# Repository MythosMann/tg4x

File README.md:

The TG4x
A cheap, opensource, qmk powered 40%.
Summary
Basically, this would be a ~$30-35 qmk powered 40% keyboard using parts from a "cop car" keyboard.  The name comes from the fact that it's a step up (TG4x), but also that it's a 40%(think 4x%).  Since the TG3's are so cheap, and they come with switches (mx blacks, too), caps, and plates, they're a great start for a handwired build.  However, not many people have the time or resources to make a handwired build.  I wnated to make something that's more fun than buying a Redragon k552, but at the same price point.  My goal for this project is to drag more people down into the wallet-sucking abyss, without sucking people's wallets.
How it would work:
I'd probably sell it three ways; a barebones kit, a kit with everything you'd need, and fully assembled keyboards.  
- The barebones kits would be the pcbs, diodes, standoffs, and a pre-programmed controller.  You'd need to buy your own TG3 and cut the plates yourself.

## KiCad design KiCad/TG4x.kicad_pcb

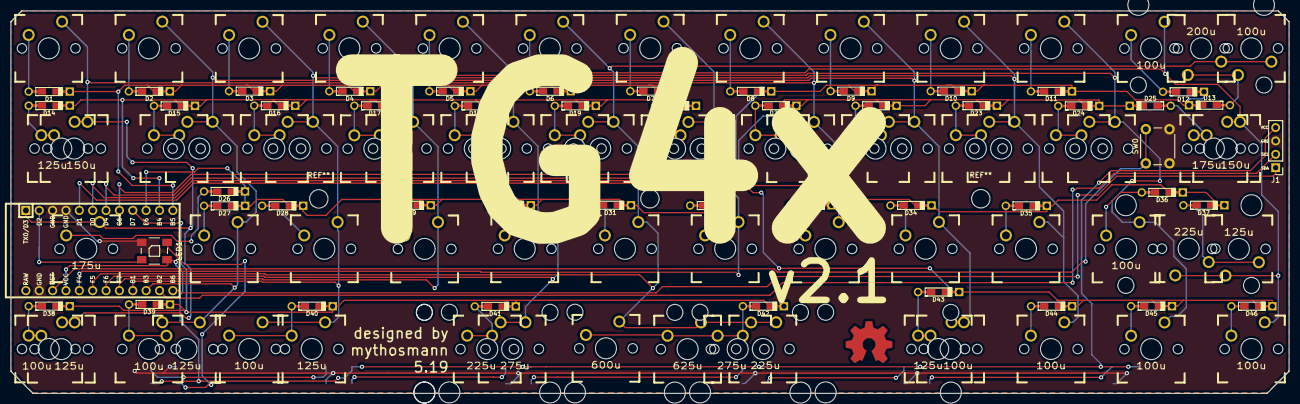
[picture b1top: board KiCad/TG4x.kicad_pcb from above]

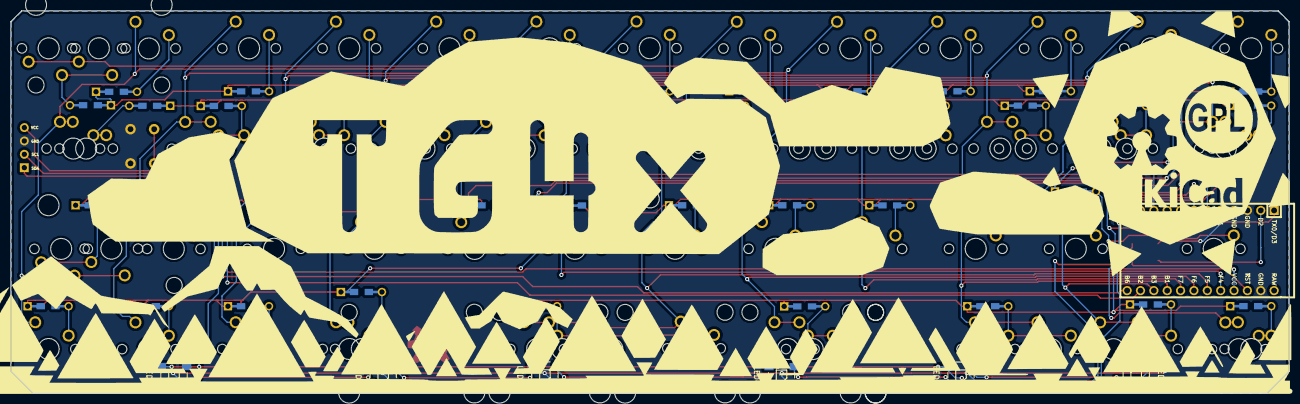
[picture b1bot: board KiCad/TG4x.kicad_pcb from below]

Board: 2 copper layers, 243.0 x 72.7 mm, 124 parts (7 on the bottom side), 73 nets.

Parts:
100u, 100u#2, 100u#3, 100u#4, 100u#5, 100u#6, 100u#7, 100u#8, 100u#9, 100u#10, 125u, 600u: SW_Push; MX_PCB_100H
125u#2, 125u#3, 125u#4, 125u#5, 125u#6: SW_Push; MX_PCB_125H
150u, 175u#2: SW_Push; MX_PCB_150H
150u#2, 175u: SW_Push; MX_PCB_175H
200u: SW_Push; MX_PCB_200H
225u, 225u#2, 225u#3: SW_Push; MX_PCB_225H
275u, 275u#2: SW_Push; MX_PCB_275H
625u: SW_Push; MX_PCB_625H
D1, D2, D3, D4, D5, D6, D7, D8, D9, D10, D11, D12, D13, D14, D15, D16, D17, D18, D19, D20, D21, D22, D23, D24, D25, D26, D27, D28, D29, D30, D31, D32, D33, D34, D35, D36, D37, D38, D39, D40, D41, D42, D43, D44, D45, D46: 1N4148; Diode-dual
J1: Conn_01x04_Female; PinHeader_1x04_P2.54mm_Vertical
LED1, LED2, LED3, LED4, LED5, LED6, LED7: WS2812B
SW0: SW_Push; SW_PUSH_6mm
SW1, SW2, SW3, SW4, SW5, SW6, SW7, SW8, SW9, SW10, SW11, SW15, SW15b1, SW16, SW16b1, SW17, SW17b1, SW18, SW18b1, SW19, SW19b1, SW20, SW20b1, SW21, SW21b1, SW22, SW22b1, SW23, SW23b1, SW24, SW24b1, SW27, SW28, SW29, SW30, SW31, SW32, SW33, SW34, SW35: SW_Push; MX_PCB_100H
U1: ProMicro; ArduinoProMicro

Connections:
COL0: 100u#6.1, 125u#2.1, 125u#4.1, 150u.1, 175u.1, SW1.1, SW8.1, SW21.1, SW21b1.1, SW33.1, U1.1
COL1: 100u#7.1, 100u#9.1, 125u.1, 125u#5.1, SW2.1, SW9.1, SW15.1, SW15b1.1, SW22.1, SW22b1.1, SW27.1, SW34.1, U1.15
COL2: 100u#2.1, 100u#8.1, 125u#6.1, SW3.1, SW10.1, SW16.1, SW16b1.1, SW23.1, SW23b1.1, SW28.1, SW35.1, U1.16
COL3: 100u.1, 100u#3.1, SW4.1, SW11.1, SW17.1, SW17b1.1, SW24.1, SW24b1.1, SW29.1, U1.17
COL4: 100u#4.1, 100u#5.1, 125u#3.1, 150u#2.1, 175u#2.1, 225u.1, 225u#2.1, 275u#2.1, SW5.1, SW18.1, SW18b1.1, SW30.1, U1.18
COL5: 100u#10.2, 200u.2, 225u#3.1, 275u.1, 600u.1, 625u.1, SW6.1, SW19.1, SW19b1.1, SW31.1, U1.19
COL6: SW7.1, SW20.1, SW20b1.1, SW32.1, U1.20
GND: J1.3, LED1.3, LED2.3, LED3.3, LED4.3, LED5.3, LED6.3, LED7.3, SW0.2, U1.3, U1.4, U1.23
LED: LED1.4, U1.2
unnamed: D1.2, SW1.2
unnamed: D2.2, SW2.2
unnamed: D3.2, SW3.2
unnamed: D4.2, SW4.2
unnamed: D5.2, SW5.2
unnamed: D6.2, SW6.2
unnamed: D7.2, SW7.2
unnamed: D8.2, SW8.2
unnamed: D9.2, SW9.2
unnamed: D10.2, SW10.2
unnamed: D11.2, SW11.2
unnamed: 100u#5.2, D12.2
unnamed: 100u#10.1, 200u.1, D13.2
unnamed: 125u#2.2, 150u.2, D14.2
unnamed: D15.2, SW15.2, SW15b1.2
unnamed: D16.2, SW16.2, SW16b1.2
unnamed: D17.2, SW17.2, SW17b1.2
unnamed: D18.2, SW18.2, SW18b1.2
unnamed: D19.2, SW19.2, SW19b1.2
unnamed: D20.2, SW20.2, SW20b1.2
unnamed: D21.2, SW21.2, SW21b1.2
unnamed: D22.2, SW22.2, SW22b1.2
unnamed: D23.2, SW23.2, SW23b1.2
unnamed: D24.2, SW24.2, SW24b1.2
unnamed: 150u#2.2, 175u#2.2, D25.2
unnamed: 175u.2, D26.2
unnamed: D27.2, SW27.2
unnamed: D28.2, SW28.2
unnamed: D29.2, SW29.2
unnamed: D30.2, SW30.2
unnamed: D31.2, SW31.2
unnamed: D32.2, SW32.2
unnamed: D33.2, SW33.2
unnamed: D34.2, SW34.2
unnamed: D35.2, SW35.2
unnamed: 100u.2, D36.2
unnamed: 125u#3.2, 225u.2, D37.2
unnamed: 100u#6.2, 125u#4.2, D38.2
unnamed: 100u#7.2, 125u#5.2, D39.2
unnamed: 100u#8.2, 125u#6.2, D40.2
unnamed: 225u#2.2, 275u#2.2, D41.2
unnamed: 225u#3.2, 275u.2, 600u.2, 625u.2, D42.2
unnamed: 100u#9.2, 125u.2, D43.2
unnamed: 100u#2.2, D44.2
unnamed: 100u#3.2, D45.2
unnamed: 100u#4.2, D46.2
unnamed: LED1.2, LED2.4
unnamed: LED2.2, LED3.4
unnamed: LED3.2, LED4.4
unnamed: LED4.2, LED5.4
unnamed: LED5.2, LED6.4
unnamed: LED6.2, LED7.4
ROW0: D1.1, D2.1, D3.1, D4.1, D5.1, D6.1, D7.1, U1.12
ROW1: D14.1, D15.1, D16.1, D17.1, D18.1, D19.1, D20.1, U1.11
ROW2: D26.1, D27.1, D28.1, D29.1, D30.1, D31.1, D32.1, U1.10
ROW3: D38.1, D39.1, D40.1, D41.1, D42.1, U1.9
ROW4: D8.1, D9.1, D10.1, D11.1, D12.1, D13.1, U1.8
ROW5: D21.1, D22.1, D23.1, D24.1, D25.1, U1.7
ROW6: D33.1, D34.1, D35.1, D36.1, D37.1, U1.6
ROW7: D43.1, D44.1, D45.1, D46.1, U1.5
RST: SW0.1, U1.22
SCL: J1.2, U1.14
SDA: J1.1, U1.13
VCC: J1.4, LED1.1, LED2.1, LED3.1, LED4.1, LED5.1, LED6.1, LED7.1, U1.21

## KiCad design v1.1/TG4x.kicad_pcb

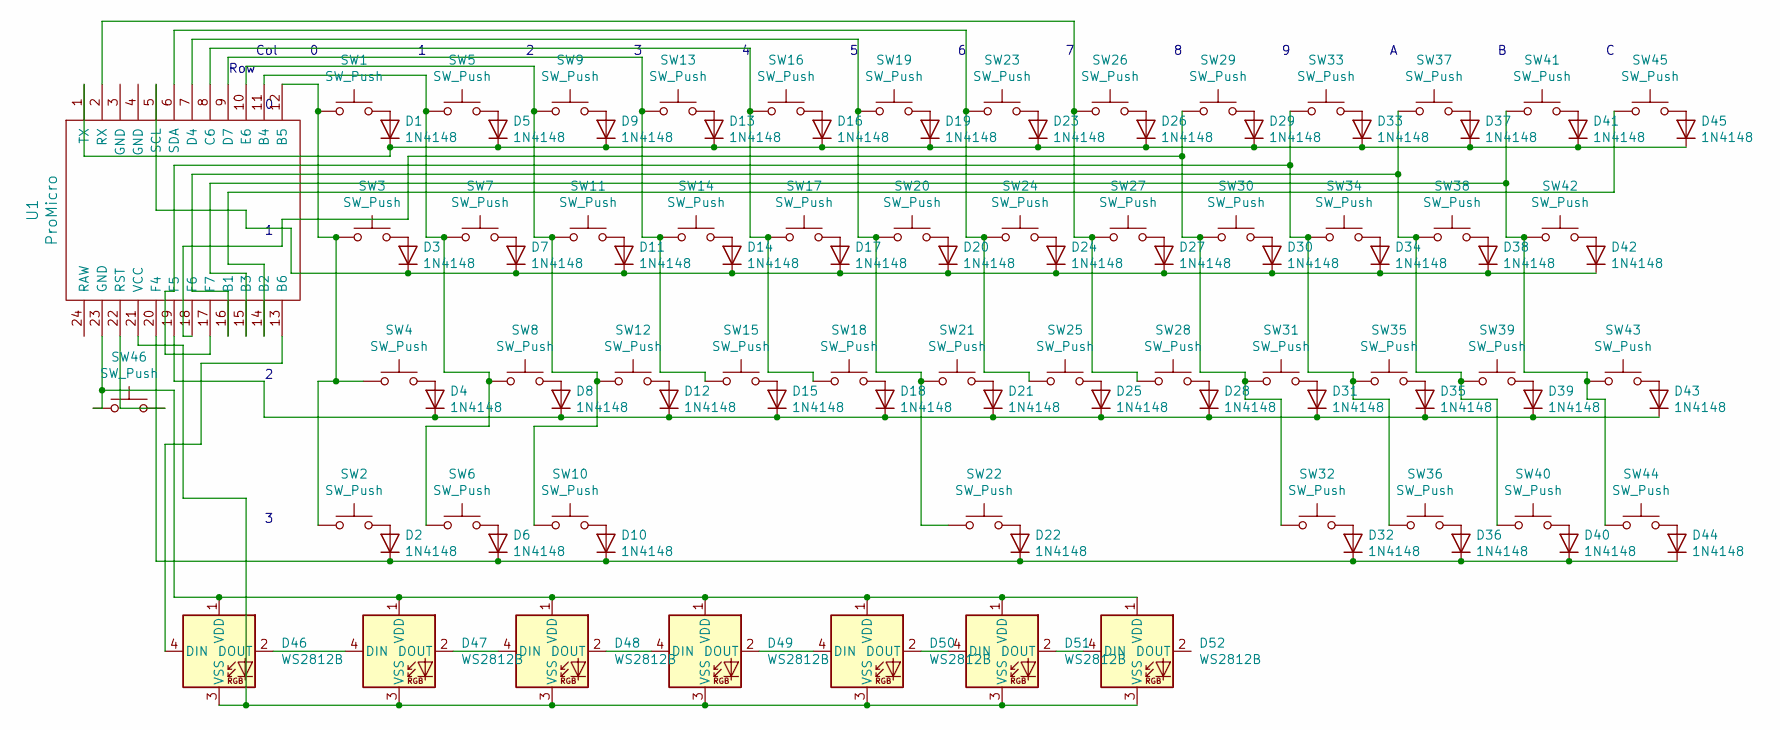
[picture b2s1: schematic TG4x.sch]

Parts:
D1, D2, D3, D4, D5, D6, D7, D8, D9, D10, D11, D12, D13, D14, D15, D16, D17, D18, D19, D20, D21, D22, D23, D24, D25, D26, D27, D28, D29, D30, D31, D32, D33, D34, D35, D36, D37, D38, D39, D40, D41, D42, D43, D44, D45: 1N4148; D_DO-35_SOD27_P7.62mm_Horizontal
D46, D47, D48, D49, D50, D51, D52: WS2812B; LED_WS2812B_PLCC4_5.0x5.0mm_P3.2mm
SW1, SW2, SW5, SW6, SW7, SW8, SW9, SW10, SW11, SW12, SW13, SW14, SW15, SW16, SW17, SW18, SW19, SW20, SW21, SW22, SW23, SW24, SW25, SW26, SW27, SW28, SW29, SW30, SW31, SW32, SW33, SW34, SW35, SW36, SW37, SW38, SW39, SW40, SW41, SW44, SW45: SW_Push; SW_Cherry_MX1A_1.00u_Plate
SW3, SW43: SW_Push; SW_Cherry_MX1A_1.25u_Plate
SW4, SW42: SW_Push; SW_Cherry_MX1A_1.75u_Plate
SW46: SW_Push; SW_PUSH_6mm
U1: ProMicro

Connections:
unnamed: D1.1 (K), D5.1 (K), D9.1 (K), D13.1 (K), D16.1 (K), D19.1 (K), D23.1 (K), D26.1 (K), D29.1 (K), D33.1 (K), D37.1 (K), D41.1 (K), D45.1 (K), U1.1 (TX)
unnamed: D1.2 (A), SW1.2
unnamed: D2.2 (A), SW2.2
unnamed: D3.2 (A), SW3.2
unnamed: D4.2 (A), SW4.2
unnamed: D5.2 (A), SW5.2
unnamed: D6.2 (A), SW6.2
unnamed: D7.2 (A), SW7.2
unnamed: D8.2 (A), SW8.2
unnamed: D9.2 (A), SW9.2
unnamed: D2.1 (K), D6.1 (K), D10.1 (K), D22.1 (K), D32.1 (K), D36.1 (K), D40.1 (K), D44.1 (K), U1.20 (F4)
unnamed: D10.2 (A), SW10.2
unnamed: D3.1 (K), D7.1 (K), D11.1 (K), D14.1 (K), D17.1 (K), D20.1 (K), D24.1 (K), D27.1 (K), D30.1 (K), D34.1 (K), D38.1 (K), D42.1 (K), U1.5 (SCL)
unnamed: D11.2 (A), SW11.2
unnamed: D4.1 (K), D8.1 (K), D12.1 (K), D15.1 (K), D18.1 (K), D21.1 (K), D25.1 (K), D28.1 (K), D31.1 (K), D35.1 (K), D39.1 (K), D43.1 (K), U1.19 (F5)
unnamed: D12.2 (A), SW12.2
unnamed: D13.2 (A), SW13.2
unnamed: D14.2 (A), SW14.2
unnamed: D15.2 (A), SW15.2
unnamed: D16.2 (A), SW16.2
unnamed: D17.2 (A), SW17.2
unnamed: D18.2 (A), SW18.2
unnamed: D19.2 (A), SW19.2
unnamed: D20.2 (A), SW20.2
unnamed: D21.2 (A), SW21.2
unnamed: D22.2 (A), SW22.2
unnamed: D23.2 (A), SW23.2
unnamed: D24.2 (A), SW24.2
unnamed: D25.2 (A), SW25.2
unnamed: D26.2 (A), SW26.2
unnamed: D27.2 (A), SW27.2
unnamed: D28.2 (A), SW28.2
unnamed: D29.2 (A), SW29.2
unnamed: D30.2 (A), SW30.2
unnamed: D31.2 (A), SW31.2
unnamed: D32.2 (A), SW32.2
unnamed: D33.2 (A), SW33.2
unnamed: D34.2 (A), SW34.2
unnamed: D35.2 (A), SW35.2
unnamed: D36.2 (A), SW36.2
unnamed: D37.2 (A), SW37.2
unnamed: D38.2 (A), SW38.2
unnamed: D39.2 (A), SW39.2
unnamed: D40.2 (A), SW40.2
unnamed: D41.2 (A), SW41.2
unnamed: D42.2 (A), SW42.2
unnamed: D43.2 (A), SW43.2
unnamed: D44.2 (A), SW44.2
unnamed: D45.2 (A), SW45.2
unnamed: D46.1 (VDD), D47.1 (VDD), D48.1 (VDD), D49.1 (VDD), D50.1 (VDD), D51.1 (VDD), D52.1 (VDD), SW46.1, U1.23 (GND)
unnamed: D46.2 (DOUT), D47.4 (DIN)
unnamed: D46.3 (VSS), D47.3 (VSS), D48.3 (VSS), D49.3 (VSS), D50.3 (VSS), D51.3 (VSS), D52.3 (VSS), U1.21 (VCC)
unnamed: D46.4 (DIN), U1.13 (B6)
unnamed: D47.2 (DOUT), D48.4 (DIN)
unnamed: D48.2 (DOUT), D49.4 (DIN)
unnamed: D49.2 (DOUT), D50.4 (DIN)
unnamed: D50.2 (DOUT), D51.4 (DIN)
unnamed: D51.2 (DOUT), D52.4 (DIN)
unnamed: SW1.1, SW2.1, SW3.1, SW4.1, U1.12 (B5)
unnamed: SW5.1, SW6.1, SW7.1, SW8.1, U1.11 (B4)
unnamed: SW9.1, SW10.1, SW11.1, SW12.1, U1.10 (E6)
unnamed: SW13.1, SW14.1, SW15.1, U1.9 (D7)
unnamed: SW16.1, SW17.1, SW18.1, U1.8 (C6)
unnamed: SW19.1, SW20.1, SW21.1, SW22.1, U1.7 (D4)
unnamed: SW23.1, SW24.1, SW25.1, U1.6 (SDA)
unnamed: SW26.1, SW27.1, SW28.1, U1.2 (RX)
unnamed: SW29.1, SW30.1, SW31.1, SW32.1, U1.18 (F6)
unnamed: SW33.1, SW34.1, SW35.1, SW36.1, U1.17 (F7)
unnamed: SW37.1, SW38.1, SW39.1, SW40.1, U1.16 (B1)
unnamed: SW41.1, SW42.1, SW43.1, SW44.1, U1.15 (B3)
unnamed: SW45.1, U1.14 (B2)
unnamed: SW46.2, U1.22 (RST)

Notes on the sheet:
Col
Row

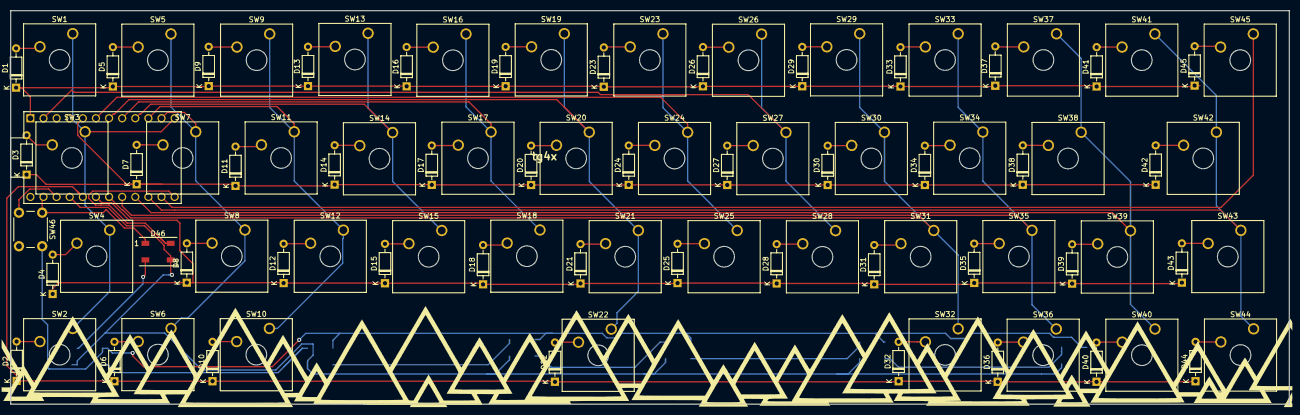
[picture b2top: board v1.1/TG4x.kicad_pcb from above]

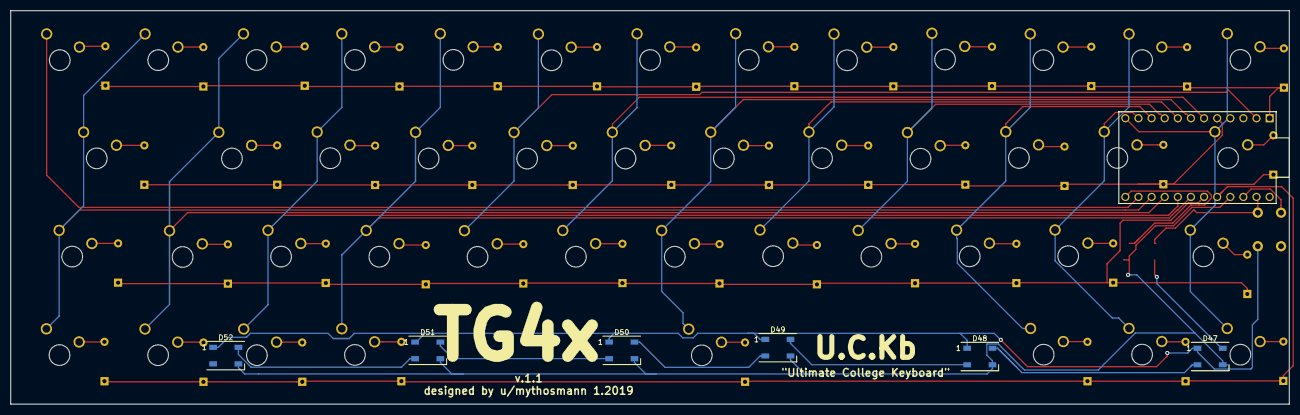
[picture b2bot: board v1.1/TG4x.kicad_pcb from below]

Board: 2 copper layers, 247.6 x 76.2 mm, 99 parts (7 on the bottom side), 72 nets.

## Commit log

2019-01-23 Added KiCad files for first revision.
    The KiCad Libraries, Schematic, pcb, and gerber files.
2019-01-23 Added intital qmk files
    These aren't close to functional yet, I'm mostly just figuring out how to use github.
2019-01-23 Added initial qmk files
    These are nowhere near done, but I'm trying to figure out github.
2019-01-23 organized all files together
    Put everything together locally, hopefully made things more organized.
2019-01-23 Trying to organize lol
2019-01-23 Fixed column/row pins being reversed, enabled KNRO, Added imgur link
2019-01-23 default keymap
2019-01-23 Added function layer mapping, added underglow layer caps indication
2019-01-23 Shifted some diode footprints
2019-01-23 remove redundant code
2019-01-23 fixed matrix naming
2019-01-23 updated caps lock code
2019-01-23 removed LED Sleep
2019-01-23 changed rgb effect to rgb_test
2019-01-23 disabled console and commands in rules.mk
2019-01-24 Update Pro micro footprint
    Now uses keebio's staggered footprint
2019-01-24 rollback
2019-01-24 Changed image files
2019-01-24 Updated readmes
2019-01-25 Added .dxf and .ai for plates
2019-01-25 changed image name for readme
2019-01-25 Added middle standoff holes
2019-01-27 fixed mouting holes
2019-01-29 added silkscreen
2019-01-29 added mounting holes, fixed traces, updated gerbers
2019-01-29 Adding Tap Dance Support to qmk files.
2019-01-29 Added tap dance to rules and keymap
2019-01-29 Added mouse control
2019-01-29 updated keymap, re-enabled LEDs
2019-01-29 updated pcb graphic
2019-01-29 Create LICENSE
2019-01-29 pcb graphics
2019-01-29 changed thumbs
2019-01-29 gerbers
2019-01-30 updated gerbers, switch plate files
2019-01-30 new render, updated case files
2019-02-01 started moving to kailh hotswap
2019-02-01 changed footprints to 5 pin
2019-02-01 Fixed traces for 5 pin
2019-02-01 Updated gerbers for 5 pin
2019-02-02 moved some diodes and traces
2019-02-05 Fixed traces, leds
    moved some of the traces that were too close to holes, moved leds out from under holes
2019-02-06 updated to staggered pro micro footprint
2019-02-07 updated pics
2019-02-08 moved spacebar switch footprint
2019-02-08 moved left hand diodes in
2019-02-08 added clearance for standoffs
2019-02-08 finished adding standoff clearance
2019-02-09 Changing pcb Graphic
2019-02-09 Organized image files, finished graphic
2019-02-10 Fixed LED Polaarity, uppdated to v1.2
2019-02-11 Updated graphic and thummbnails
2019-02-11 slightly changed edge cut
2019-02-12 Updated readme with prices
2019-02-12 Labeled Code
2019-02-13 rgb testing
2019-02-19 removed comment
2019-02-19 trimmed top and bottom.
2019-02-19 scaled graphic to new pcb
2019-02-19 shrunk column labelling
2019-02-19 removed switch labels from f.silk
2019-02-22 updated rgb code
2019-02-24 updated gerber files
2019-02-24 updated gerbers, started on platge stencil
2019-02-24 gerbers again
2019-02-24 changed gerber settings
2019-02-25 updated gerbers once again
2019-02-27 updated gerbers
2019-03-18 added additional switch footprints to pcb
2019-03-20 moved sw3 footprint up
2019-03-20 moved sw3 up
2019-03-24 removed footprints
2019-03-25 cleared pcb, added switches to schematic
2019-03-26 replaced pro micro with stm32
2019-03-27 updated schematic, added all switch footprints
2019-04-21 stuff
2019-04-21 More Work
    Finished schematic, started pcb footprints, updated annotations, new netlist
2019-04-22 removed hotswap sockets
    no linger going to use hotswap sockets, they don't work with all the layouts.
2019-04-30 v2 release
2019-04-30 added plates
2019-04-30 gerber files
2019-04-30 switch plate changes
2019-05-02 release for v2.0
2019-05-02 updated readme and pic
2019-05-03 organized files, yay
2019-05-04 added default keymaps and layers
2019-05-11 v.2.1
2019-05-14 updated for interest check
2019-05-14 update and add pics
2019-05-15 updated gerbers, added pic
2019-05-20 new gerbers
2019-05-29 minor aesthetic changes
2019-05-29 Updated LED footprint
2019-06-01 updated keymaps
2019-06-08 resized image
2019-08-15 added build guide pics
2019-08-15 renamed build guide pics
